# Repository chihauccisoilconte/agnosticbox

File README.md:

# Agnostic Box

This repository contains the files necessary to make an Agnostic Box.

The Agnostic Box is a versatile DMI (Digital Musical Instrument) that can be programmed in many ways. It is powered by an Arduino Nano ESP32, so it can run different interactive music, sound, and sensor-based sketches; this repository provides example sketches using the Mozzi audio synthesis library. The box is equipped with three potentiometers, three buttons, three LEDs, an MPU6050/GY-521 motion sensor connected over I2C, and a PAM8302A amplifier, giving it a compact set of tactile, visual, motion, and audio features for building custom musical interactions.

## Author

Created by [chihauccisoilconte](https://chihauccisoilconte.eu/).

The Agnostic Box is an idea by Raul Masu and Nicolo Merendino (aka chi ha ucciso il conte?).

## Contents

- `agnostic box instruction manual.pdf` - build and assembly documentation.
- `agnostic box PCB/` - KiCad PCB files, Gerber files, drill files, PCB exports, and related PCB assets.
- `agonstic box 3D models/` - FreeCAD source files and STL/3MF files for 3D-printed parts.
- `agnostic box 2d vectors/` - 2D vector files and sticker artwork.
- `agnostic box arduino nano esp32 code/` - Arduino Nano ESP32 sketches.

## License

MIT License

Copyright (c) 2026 chihauccisoilconte

Permission is hereby granted, free of charge, to any person obtaining a copy
of this repository and associated documentation files (the "Work"), to deal
in the Work without restriction, including without limitation the rights
to use, copy, modify, merge, publish, distribute, sublicense, and/or sell
copies of the Work, and to permit persons to whom the Work is furnished to do
so, subject to the following conditions:

The above copyright notice and this permission notice shall be included in all
copies or substantial portions of the Work.

THE WORK IS PROVIDED "AS IS", WITHOUT WARRANTY OF ANY KIND, EXPRESS OR
IMPLIED, INCLUDING BUT NOT LIMITED TO THE WARRANTIES OF MERCHANTABILITY,
FITNESS FOR A PARTICULAR PURPOSE AND NONINFRINGEMENT. IN NO EVENT SHALL THE
AUTHORS OR COPYRIGHT HOLDERS BE LIABLE FOR ANY CLAIM, DAMAGES OR OTHER
LIABILITY, WHETHER IN AN ACTION OF CONTRACT, TORT OR OTHERWISE, ARISING FROM,
OUT OF OR IN CONNECTION WITH THE WORK OR THE USE OR OTHER DEALINGS IN THE
WORK.

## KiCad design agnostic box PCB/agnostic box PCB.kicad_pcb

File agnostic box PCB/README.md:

# Agnostic Box PCB

This folder contains the PCB files for the Agnostic Box.

The PCB was made with [KiCad](https://www.kicad.org/), an open source electronics design suite. The folder includes KiCad project files, schematic and PCB layout files, Gerber files, drill files, board backups, graphics, footprints, and PCB export files.

Use the KiCad project files to inspect or modify the schematic and PCB layout. Use the Gerber and drill files when ordering or manufacturing the PCB.

For travel and safety, the standard Agnostic Box build does not include a battery. The PCB still includes the possibility of adding one through the battery footprint/connection, so builders can adapt the power setup if their use case requires it.

## License

MIT License

Copyright (c) 2026 chihauccisoilconte

Permission is hereby granted, free of charge, to any person obtaining a copy
of this repository and associated documentation files (the "Work"), to deal
in the Work without restriction, including without limitation the rights
to use, copy, modify, merge, publish, distribute, sublicense, and/or sell
copies of the Work, and to permit persons to whom the Work is furnished to do
so, subject to the following conditions:

The above copyright notice and this permission notice shall be included in all
copies or substantial portions of the Work.

THE WORK IS PROVIDED "AS IS", WITHOUT WARRANTY OF ANY KIND, EXPRESS OR
IMPLIED, INCLUDING BUT NOT LIMITED TO THE WARRANTIES OF MERCHANTABILITY,
FITNESS FOR A PARTICULAR PURPOSE AND NONINFRINGEMENT. IN NO EVENT SHALL THE
AUTHORS OR COPYRIGHT HOLDERS BE LIABLE FOR ANY CLAIM, DAMAGES OR OTHER
LIABILITY, WHETHER IN AN ACTION OF CONTRACT, TORT OR OTHERWISE, ARISING FROM,
OUT OF OR IN CONNECTION WITH THE WORK OR THE USE OR OTHER DEALINGS IN THE
WORK.

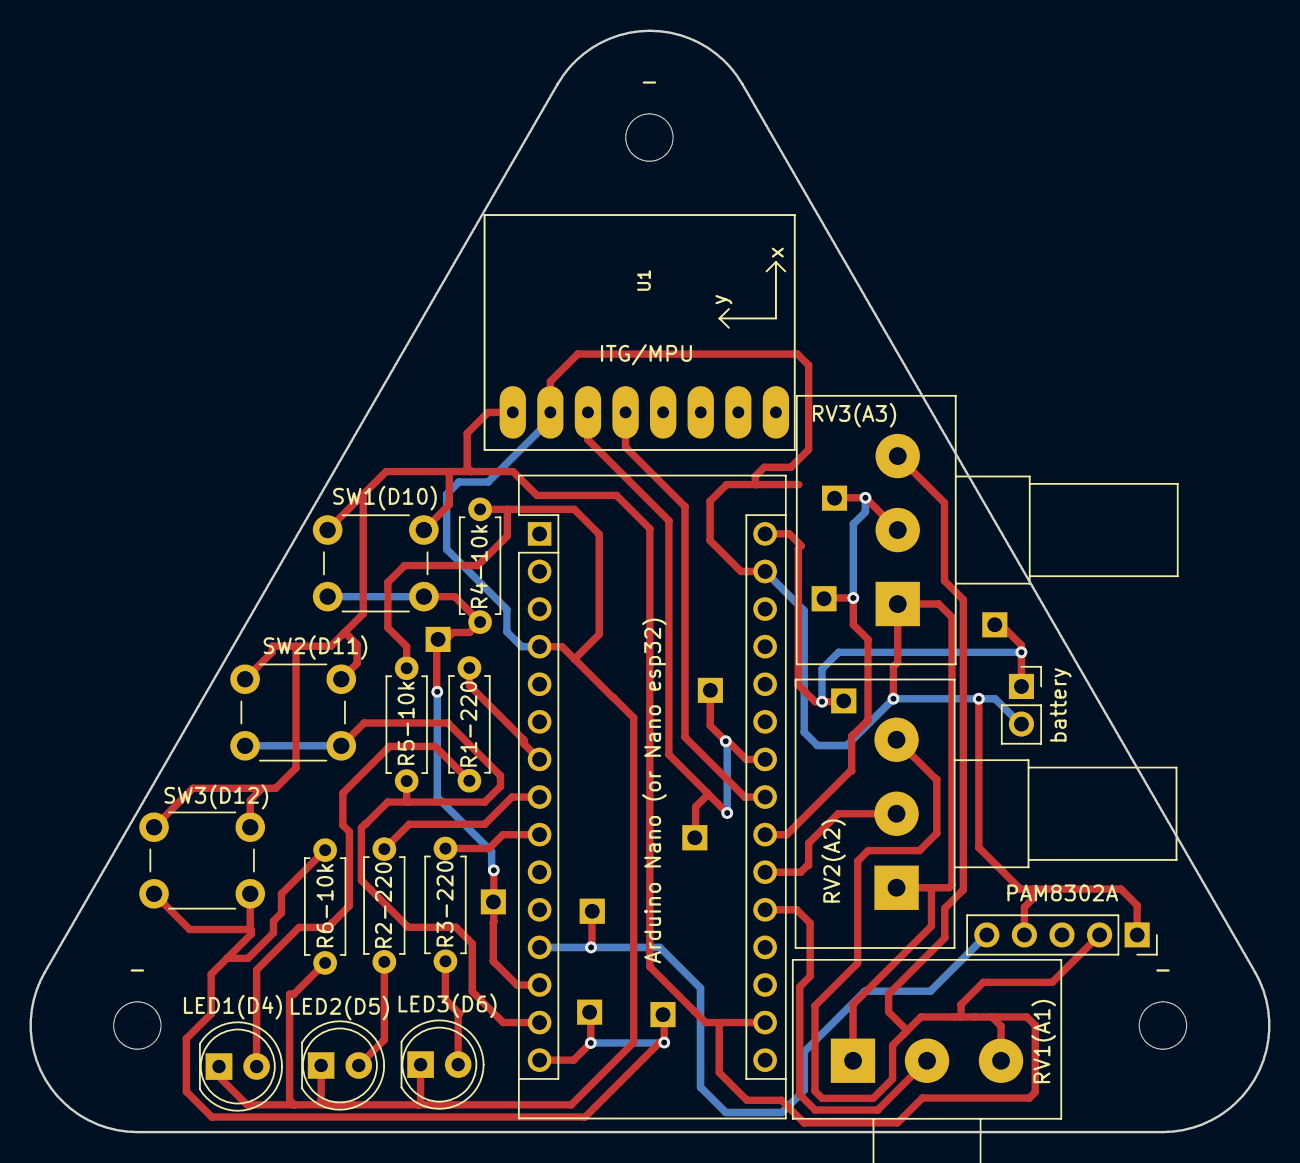
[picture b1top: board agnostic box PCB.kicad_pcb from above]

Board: 2 copper layers, 83.7 x 74.4 mm, 22 parts (0 on the bottom side), 12 nets.

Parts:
-: MountingHole_3.2mm_M3_DIN965
-#2, -#3: MountingHole_3.2mm_M3_DIN965
Arduino Nano (or Nano esp32): Arduino_Nano_v3.x; Arduino_Nano
LED1(D4), LED2(D5), LED3(D6): LED; LED_D5.0mm
PAM8302A: PAM8302A; PinSocket_1x05_P2.54mm_Vertical
R1-220, R2-220, R3-220, R4-10k, R5-10k, R6-10k: R; R_Axial_DIN0207_L6.3mm_D2.5mm_P7.62mm_Horizontal
RV1(A1), RV2(A2), RV3(A3): R_Potentiometer; Potentiometer_Alps_RK163_Single_Horizontal
SW1(D10), SW2(D11), SW3(D12): SW_DIP_x01; SW_PUSH_6mm
U1: GY-521
battery: Battery; PinSocket_1x02_P2.54mm_Vertical

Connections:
GND: Arduino Nano (or Nano esp32).4 (GND), Arduino Nano (or Nano esp32).29 (GND), LED1(D4).1 (K), LED2(D5).1 (K), LED3(D6).1 (K), PAM8302A.1, PAM8302A.4, R4-10k.2, R5-10k.2, R6-10k.1, RV1(A1).1, RV2(A2).1, RV3(A3).1, U1.GND, battery.2 (-)
unnamed: Arduino Nano (or Nano esp32).20 (A1), RV1(A1).2
unnamed: Arduino Nano (or Nano esp32).21 (A2), RV2(A2).2
unnamed: Arduino Nano (or Nano esp32).22 (A3), RV3(A3).2
unnamed: Arduino Nano (or Nano esp32).23 (A4), U1.SDA
unnamed: Arduino Nano (or Nano esp32).24 (A5), U1.SCL
unnamed: Arduino Nano (or Nano esp32).12 (D9), PAM8302A.5
unnamed: Arduino Nano (or Nano esp32).13 (D10), SW1(D10).2
unnamed: Arduino Nano (or Nano esp32).14 (D11), SW2(D11).2
unnamed: Arduino Nano (or Nano esp32).15 (D12), SW3(D12).2
unnamed: Arduino Nano (or Nano esp32).30 (VIN), battery.1 (+)
VCC: Arduino Nano (or Nano esp32).17 (3V3), PAM8302A.2, RV1(A1).3, RV2(A2).3, RV3(A3).3, SW1(D10).1, SW2(D11).1, SW3(D12).1, U1.VCC

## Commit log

2026-05-21 workshop commit
2026-05-21 Add project documentation and PCB BOM
2026-05-21 workshop commit2
2026-05-22 workshop commit3
